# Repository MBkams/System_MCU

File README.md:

# System_MCU

## Travaux pratiques : Systèmes à microcontroleurs

### 1.2 Le microcontrôleur sous KiCAD

13) Pourquoi PB9 est relié à la maase?
14) Quel est le rôle de L1, C5 et C7 ? :
    Le rôle des composants L1, C5 et C7 est de filtrer la tension d'alimentation venant du 3,3V. L'association de ces composants forme un filtre passe-bas du second ordre.

### 3. Le reste du schéma

3) Quelle page de la datasheet indique les valeurs des condensateurs ? :
   La page 1 : elle indique que la capacité doit être au moins de 0,47uF.
   La page 3 : elle indique que la capacité à une valeur typique de 1uF.
4) Quelle page de la datasheet nous indique les valeurs de condensateurs ? :
   la valeur de condensateurs des  du DAC est donnée en page 25 de la datasheet.

6) Quel est le rôle de la broche CS ?
La broche CS correspond au « Chip Enable » . Un état bas sur cette broche permet d’activer la clock et les données.

7) Quel est le rôle de la broche LDAC ?
La croche LDAC est utilisée pour transférer le registre de verrouillage d'entrée vers le registre du DAC. Lorsque cette broche est à létat bas, la sortie VOUT est mis à jour avec le contenu du registre d'entrée. 

8) Pourquoi le signal MISO n’est pas utilisé ?
Le signal MISO a été connecté directement au STM32, comme décrit dans la procédure. Le signal MOSI transmets les données du maître, le STM32, jusqu’à l’esclave et inversement pour le signal MISO (de l’esclave au maître). Comme on souhaite seulement communiquer du maître jusqu’à l’esclave, on a pas besoin d’utiliser le signal MISO.

10) Où trouve-t-on les indications du pinout du connecteur SWD ?
On trouve ces indications dans le manuel d’utilisation.

### 4. Affectation des empreintes

3) Que signifie 0805 ? 0603 ? 1206 ?
Ces informations corresponent aux dimensions des composants. Exemple avec 0805 : le composent mesure 0.08 pouces sur 0.05 pouces. (a noter que 0.1 pouce égal 2,54 mm)

4) Que signifie LQFP ? SOT-223 ? SOIC ?
QFP décrit le package du composent, cela signifie : Quad Flat Package, qui est un circuit intégré monté en surface. Et LQFP signifie : Low-profile Quad Flat Package, voulant dire que le package est plus petit que le PCB.

SOT : Small-Outline Transistor.
C'est une famille de transistor discrets pour des montages en surface.

SOIC : Small Outline Integrated Circuit 
Boîtier de circuit intégré monté en surface qui occupe une surface inférieure d’environ 30 à 50% à celle d’un boîtier double en ligne (DIP) équivalent, avec une épaisseur typique inférieure de 70%. Ils sont généralement disponibles dans les mêmes brochages que leurs homologues DIP IC. La convention pour nommer le package est SOIC ou SO suivi du nombre de broches. Par exemple, un 4011 à 14 broches serait logé dans un boîtier SOIC-14 ou SO-14. (oui ça vient de Wikipédia, mais on a lu !)

### 3.1 Activation des LL drivers

##### 2. Lors de la génération de code avec la bibliothèque LL, on remarque les changements de synthaxe des appels de fonctions.

##### 4. __STATIC_INLINE permet de définir une fonction en ligne et de la rendre statique.

##### 5. La fonction est définit aussi dans un .h . Néamoins, __STATIC_INLINE permet une optimisation au niveau compilateur lors de l'appel de fonction.

### 3.2 LED simple

##### 2. Pour une configuration du timer de la LED à une fréquence 1kHz et une résolution de 8bits, il faut déterminer les valeurs de PSC et ARR comme suivant :

- Période = (PSC + 1) * (ARR + 1) / Fréquence du clock du timer
- L'horloge du timer est à 32 Mhz. Donc PSC = 125 et ARR = 255.

### 3.3 LED avec timer

##### 3. Les valeurs de PSC et ARR sont 125 et 255 respectivement.

##### 6. La routine d'interruption se situe au nivau TIM21_IRQHandler(void).

##### 7. Avec l'utilisation de la bibliothèque LL, il doit manquer la remise à zero du flag.

##### 8. Cela peut entraîner la routine d'interuption en boucle.

##### 9. Il faut faire une remise à zero du flag.

### 3.4 UART, un simple echo

##### 5. J'ai modifié la défintion des fonctions SerialTransmit et SerialReceiveChar afin de les adapter avec HAL :)

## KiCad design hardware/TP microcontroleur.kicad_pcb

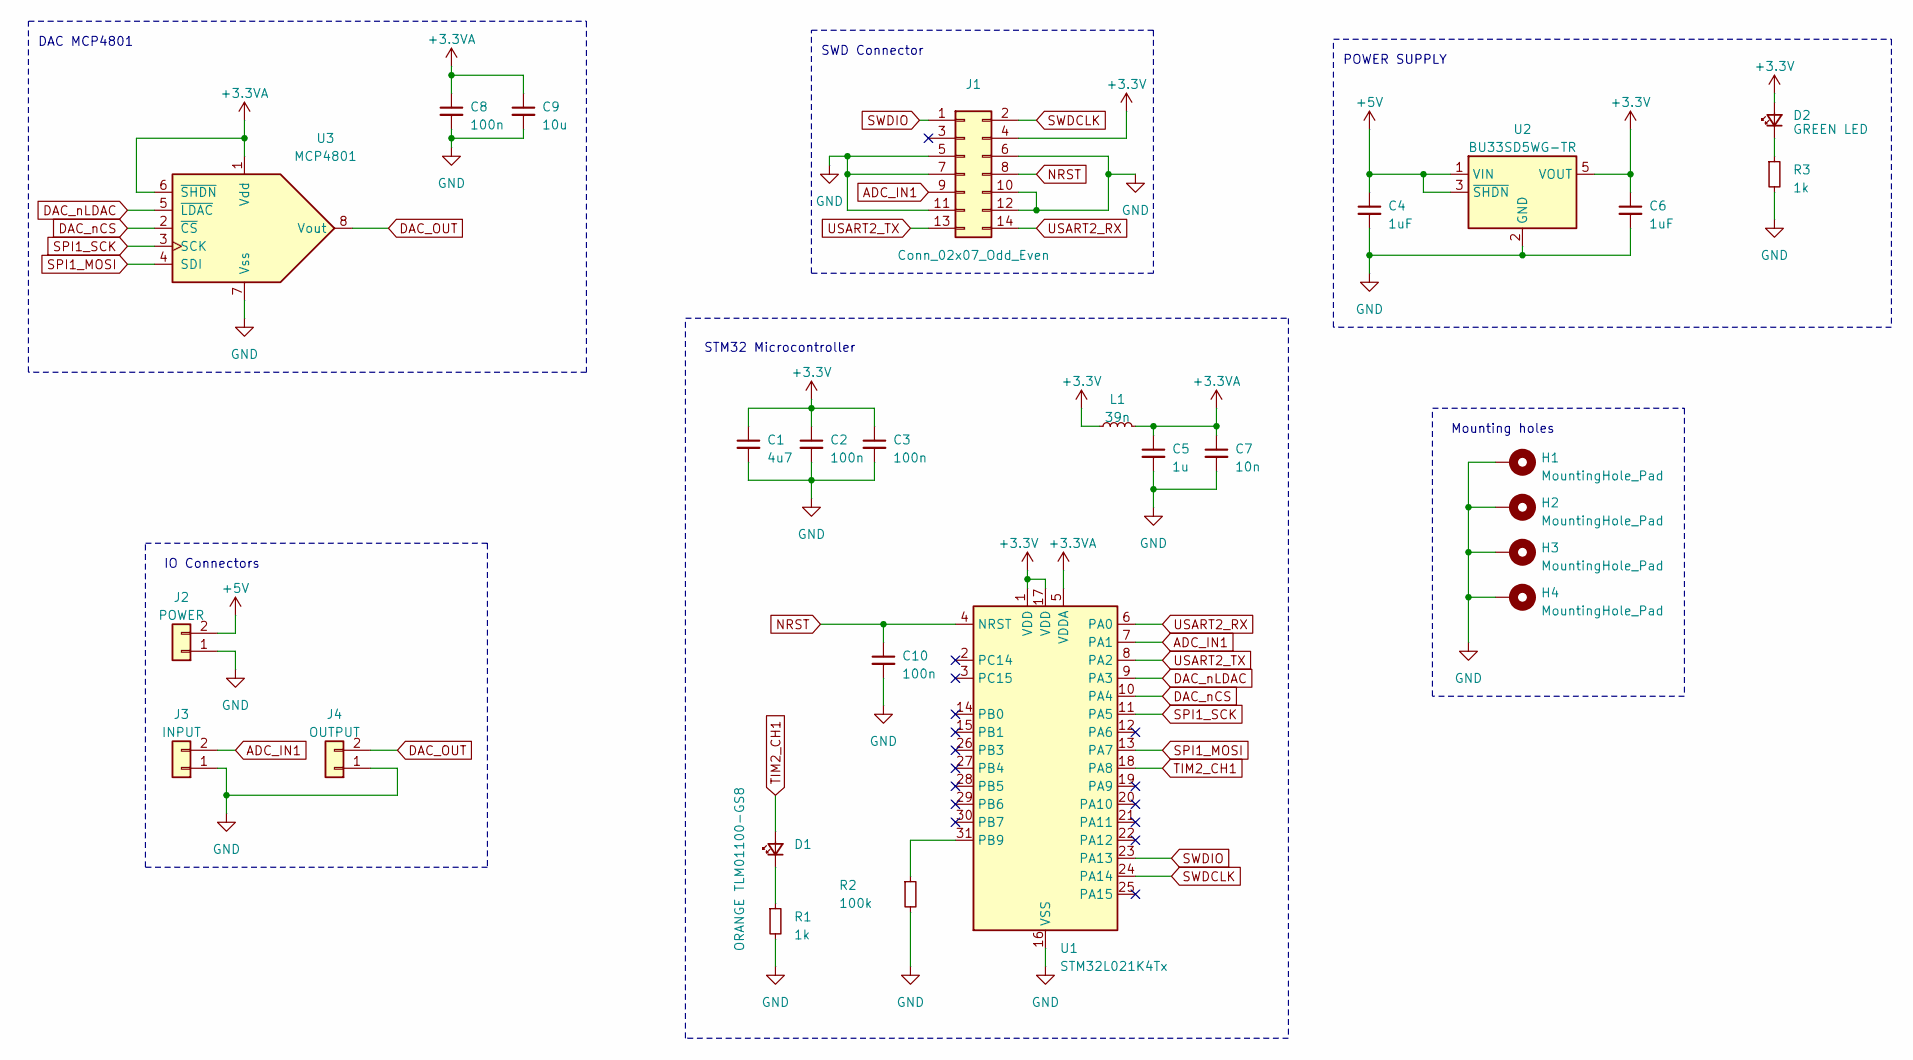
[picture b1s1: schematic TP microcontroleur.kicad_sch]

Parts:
C1: 4u7; C_0805_2012Metric_Pad1.18x1.45mm_HandSolder
C2, C3, C8, C10: 100n; C_0805_2012Metric_Pad1.18x1.45mm_HandSolder
C4, C6: 1uF; C_0805_2012Metric
C5: 1u; C_0805_2012Metric_Pad1.18x1.45mm_HandSolder
C7: 10n; C_0805_2012Metric_Pad1.18x1.45mm_HandSolder
C9: 10u; C_0805_2012Metric
D1: ORANGE TLM01100-GS8; LED_0603_1608Metric_Pad1.05x0.95mm_HandSolder
D2: GREEN LED; LED_0603_1608Metric_Pad1.05x0.95mm_HandSolder
H1, H2, H3, H4: MountingHole_Pad; MountingHole_3.2mm_M3_Pad
J1: Conn_02x07_Odd_Even; PinHeader_2x07_P1.27mm_Vertical_SMD
J2: POWER; JST_XH_B2B-XH-A_1x02_P2.50mm_Vertical
J3: INPUT; JST_XH_B2B-XH-A_1x02_P2.50mm_Vertical
J4: OUTPUT; JST_XH_B2B-XH-A_1x02_P2.50mm_Vertical
L1: 39n; L_0805_2012Metric_Pad1.05x1.20mm_HandSolder
R1, R3: 1k; R_0805_2012Metric_Pad1.20x1.40mm_HandSolder
R2: 100k; R_0805_2012Metric_Pad1.20x1.40mm_HandSolder
U1: STM32L021K4Tx; LQFP-32_7x7mm_P0.8mm
U2: BU33SD5WG-TR; SOT-23-5
U3: MCP4801; SOIC-8_3.9x4.9mm_P1.27mm

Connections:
+3.3V: C1.1, C2.1, C3.1, C6.1, D2.2 (A), J1.4, L1.1, U1.1 (VDD), U1.17 (VDD), U2.5 (VOUT)
+3.3VA: C5.1, C7.1, C8.1, C9.1, L1.2, U1.5 (VDDA), U3.1 (Vdd), U3.6 (~SHDN)
+5V: C4.1, J2.2, U2.1 (VIN), U2.3 (~SHDN)
ADC_IN1: J1.9, J3.2, U1.7 (PA1)
DAC_OUT: J4.2, U3.8 (Vout)
DAC_nCS: U1.10 (PA4), U3.2 (~CS)
DAC_nLDAC: U1.9 (PA3), U3.5 (~LDAC)
GND: C1.2, C2.2, C3.2, C4.2, C5.2, C6.2, C7.2, C8.2, C9.2, C10.2, H1.1, H2.1, H3.1, H4.1, J1.5, J1.6, J1.7, J1.10, J1.11, J1.12, J2.1, J3.1, J4.1, R1.2, R2.2, R3.2, U1.16 (VSS), U1.32 (VSS), U2.2 (GND), U3.7 (Vss)
NRST: C10.1, J1.8, U1.4 (NRST)
unnamed: D1.1 (K), R1.1
unnamed: D2.1 (K), R3.1
unnamed: R2.1, U1.31 (PB9)
SPI1_MOSI: U1.13 (PA7), U3.4 (SDI)
SPI1_SCK: U1.11 (PA5), U3.3 (SCK)
SWDCLK: J1.2, U1.24 (PA14)
SWDIO: J1.1, U1.23 (PA13)
TIM2_CH1: D1.2 (A), U1.18 (PA8)
USART2_RX: J1.14, U1.6 (PA0)
USART2_TX: J1.13, U1.8 (PA2)

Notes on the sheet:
STM32 Microcontroller
Mounting holes
IO Connectors
DAC MCP4801
POWER SUPPLY
SWD Connector

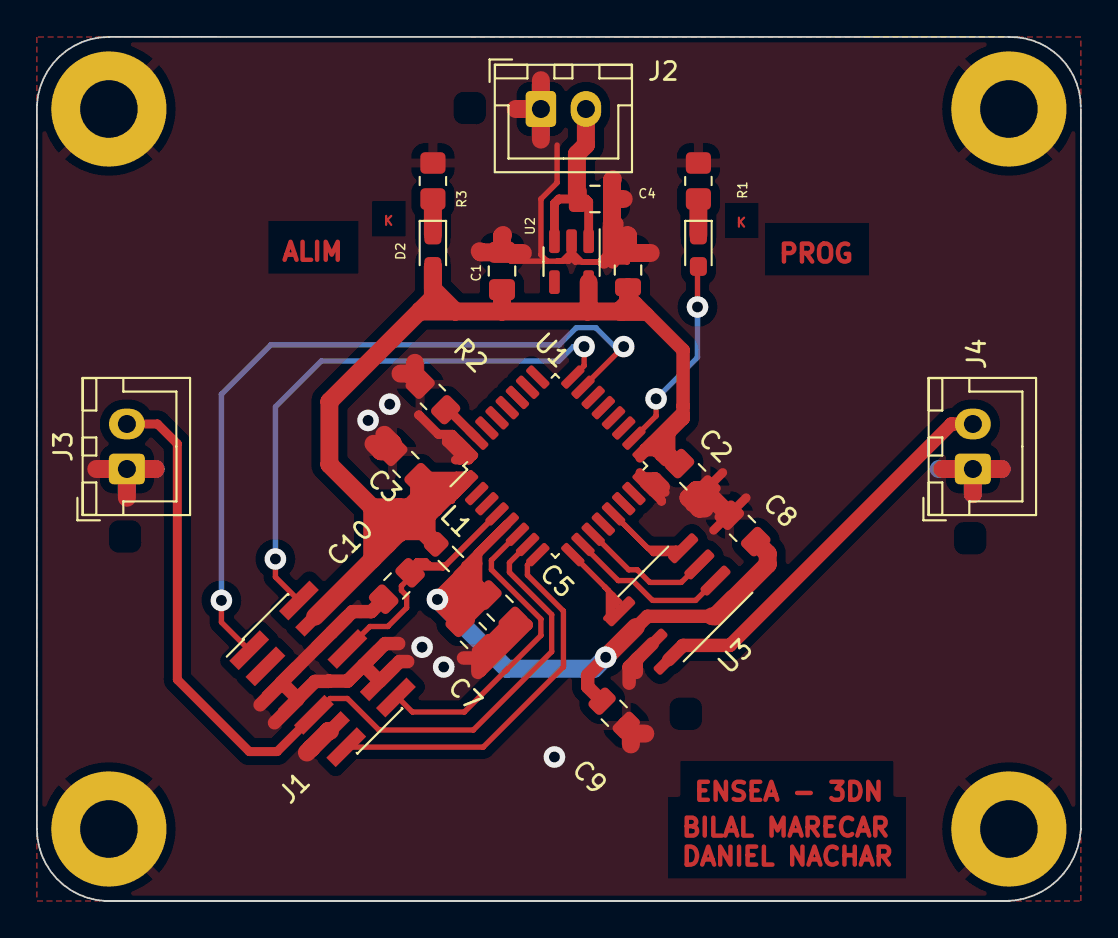
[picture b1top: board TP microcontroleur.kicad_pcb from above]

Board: 2 copper layers, 58.0 x 48.0 mm, 27 parts (0 on the bottom side), 19 nets.

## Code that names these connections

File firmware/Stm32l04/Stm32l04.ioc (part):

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Mcu.Name=STM32L021K4Tx
Mcu.Package=LQFP32
Mcu.UserName=STM32L021K4Tx
PA0-CK_IN.Mode=Asynchronous
PA0-CK_IN.Signal=USART2_RX
PA1.Mode=IN1
PA1.Signal=ADC_IN1
PA13.Mode=Serial_Wire
PA13.Signal=SYS_SWDIO
PA14.Mode=Serial_Wire
PA14.Signal=SYS_SWCLK
PA2.Mode=Asynchronous
PA2.Signal=USART2_TX
PA3.GPIOParameters=GPIO_Label
PA3.GPIO_Label=DAC_nLDAC
PA3.Signal=GPIO_Output
PA4.GPIOParameters=GPIO_Label
PA4.GPIO_Label=DAC_nCS
PA4.Signal=GPIO_Output
PA5.Mode=TX_Only_Simplex_Unidirect_Master
PA5.Signal=SPI1_SCK
PA7.Mode=TX_Only_Simplex_Unidirect_Master
PA7.Signal=SPI1_MOSI
PA8.Signal=S_TIM2_CH1
RCC.HSE_VALUE=8000000
RCC.SYSCLKFreq_VALUE=32000000
RCC.SYSCLKSource=RCC_SYSCLKSOURCE_PLLCLK
board=custom

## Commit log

2023-03-08 Project Structure
2023-03-08 MCU Board under KiCad
2023-03-08 Board schematic
2023-03-10 LED Blinker
2023-03-13 Board with PCB
2023-03-14 LED with PWM and HAL library
2023-03-15 Led Simple
2023-03-15 UART, un simple echo
2023-03-17 Questions firmware
2023-03-17 Questions hardware
